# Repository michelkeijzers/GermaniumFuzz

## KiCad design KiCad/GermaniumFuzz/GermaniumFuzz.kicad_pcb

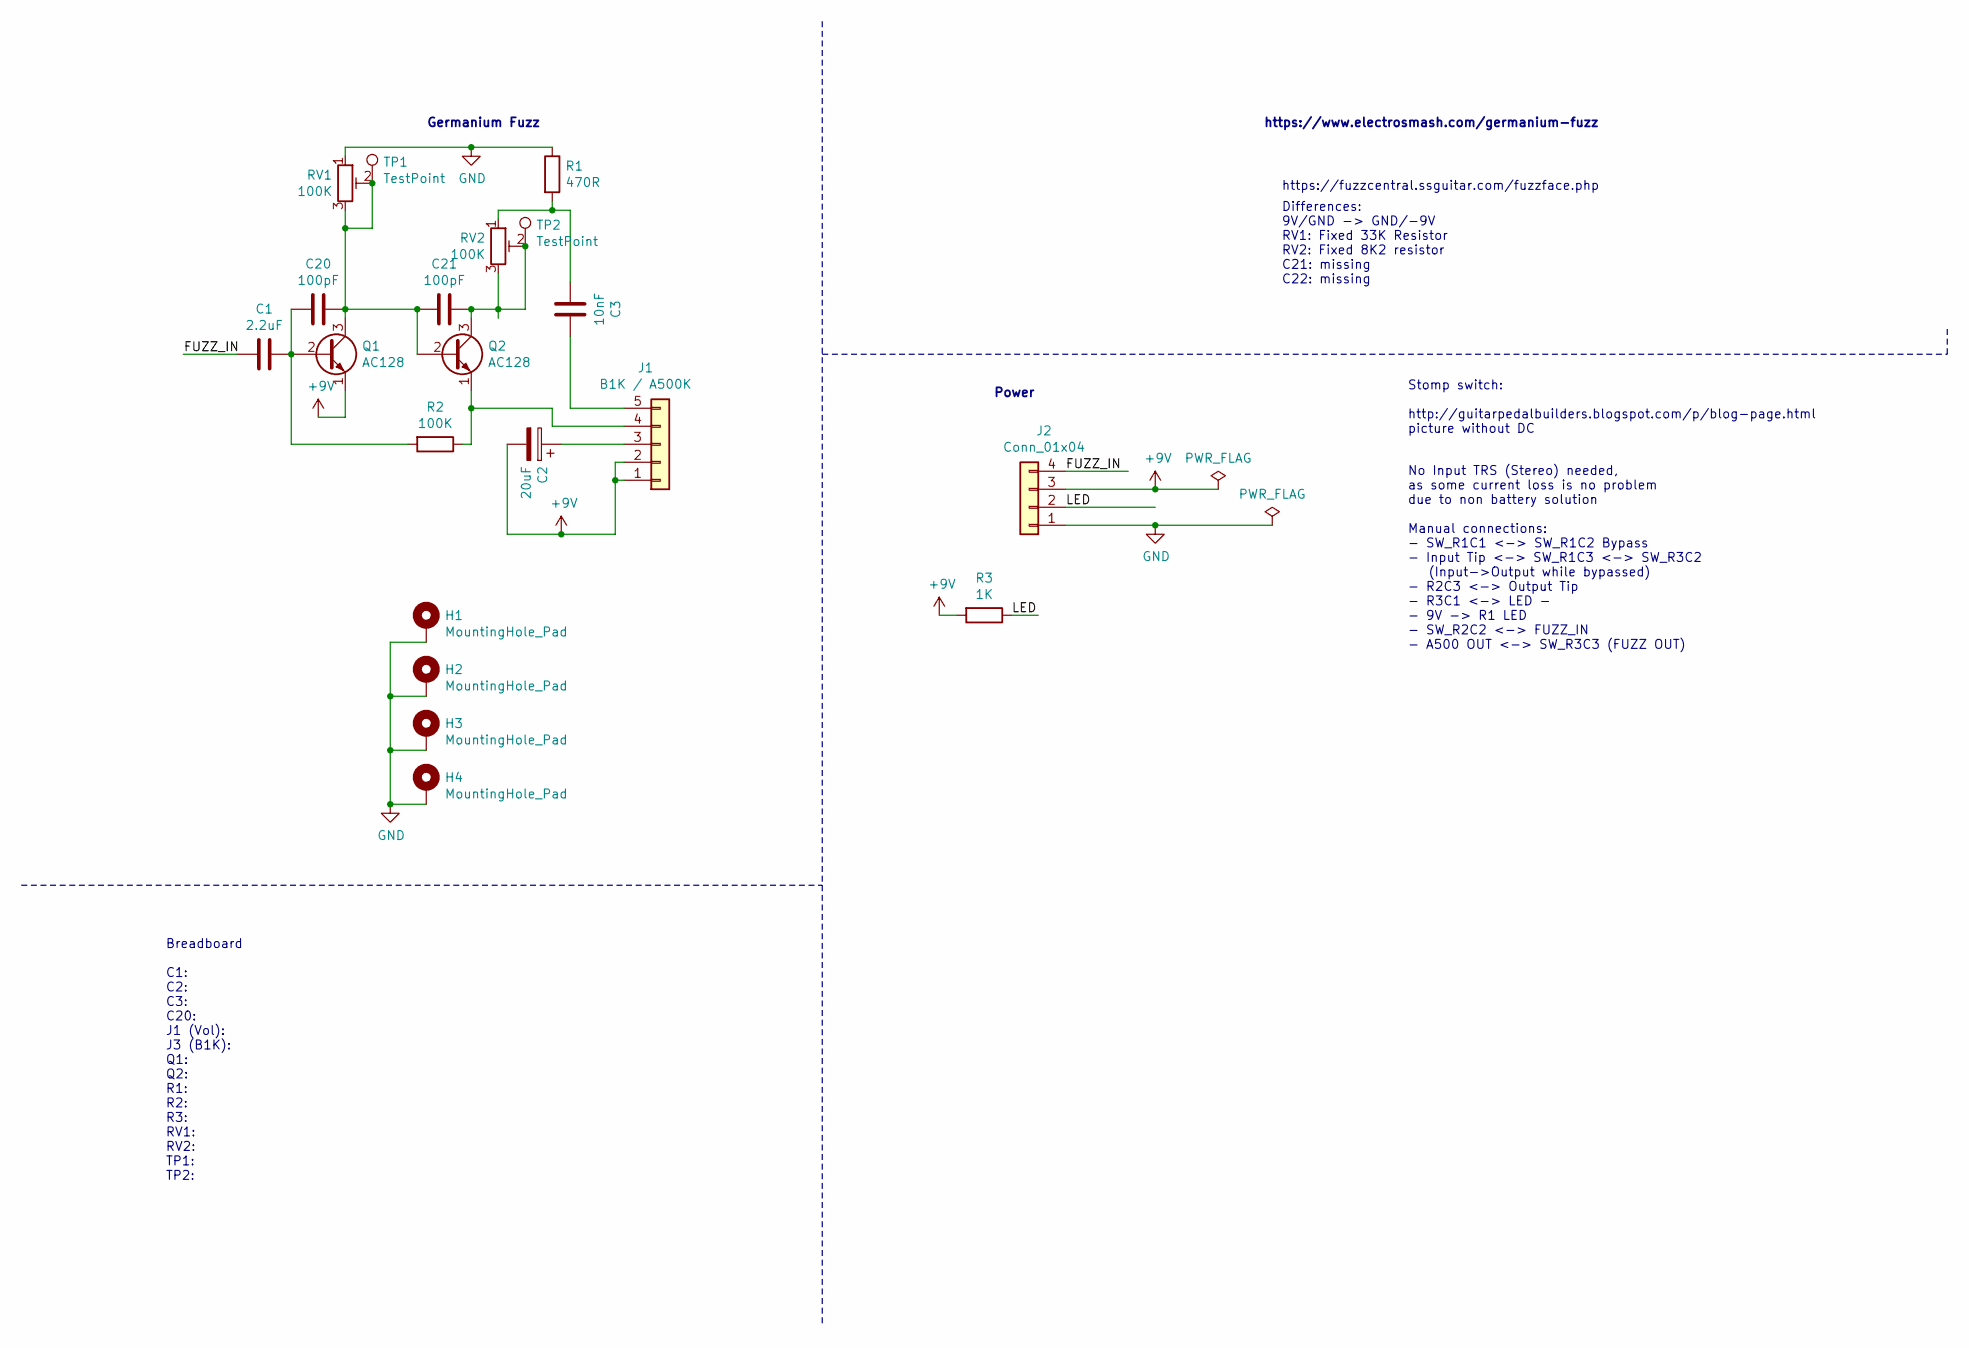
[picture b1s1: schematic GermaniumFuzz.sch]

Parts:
C1: 2.2uF; C_Disc_D3.0mm_W1.6mm_P2.50mm
C2: 20uF; C_Radial_D5.0mm_H11.0mm_P2.00mm
C3: 10nF; C_Disc_D3.0mm_W1.6mm_P2.50mm
C20, C21: 100pF; C_Disc_D3.0mm_W1.6mm_P2.50mm
H1, H2, H3, H4: MountingHole_Pad; MountingHole_3mm_Pad_Via
J1: B1K / A500K; JST_XH_B5B-XH-A_1x05_P2.50mm_Vertical
J2: Conn_01x04; JST_XH_B4B-XH-A_1x04_P2.50mm_Vertical
Q1, Q2: AC128; TO-92_Inline
R1: 470R; R_Axial_DIN0207_L6.3mm_D2.5mm_P7.62mm_Horizontal
R2: 100K; R_Axial_DIN0207_L6.3mm_D2.5mm_P7.62mm_Horizontal
R3: 1K; R_Axial_DIN0207_L6.3mm_D2.5mm_P7.62mm_Horizontal
RV1, RV2: 100K; Potentiometer_Vishay_T73XW_Horizontal
TP1, TP2: TestPoint; TestPoint_THTPad_D1.5mm_Drill0.7mm

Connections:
+9V: C2.2, J1.1, J1.2, J2.3, Q1.1 (E), R3.2
/FUZZ_IN: C1.2, J2.4
/LED: J2.2, R3.1
GND: H1.1, H2.1, H3.1, H4.1, J2.1, R1.1, RV1.1
unnamed: C1.1, C20.1, Q1.2 (B), R2.2
unnamed: C2.1, J1.3
unnamed: C3.1, J1.5
unnamed: C3.2, R1.2, RV2.1
unnamed: C20.2, C21.1, Q1.3 (C), Q2.2 (B), RV1.2, RV1.3, TP1.1
unnamed: C21.2, Q2.3 (C), RV2.2, RV2.3, TP2.1
unnamed: J1.4, Q2.1 (E), R2.1

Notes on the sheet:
https://www.electrosmash.com/germanium-fuzz
Germanium Fuzz
https://fuzzcentral.ssguitar.com/fuzzface.php
Differences: 9V/GND -> GND/-9V RV1: Fixed 33K Resistor RV2: Fixed 8K2 resistor C21: missing C22: missing
Stomp switch: http://guitarpedalbuilders.blogspot.com/p/blog-page.html picture without DC
No Input TRS (Stereo) needed, as some current loss is no problem due to non battery solution Manual connections: - SW_R1C1 <-> SW_R1C2 Bypass - Input Tip <-> SW_R1C3 <-> SW_R3C2 (Input->Output while bypassed) - R2C3 <-> Output Tip - R3C1 <-> LED - - 9V -> R1 LED - SW_R2C2 <-> FUZZ_IN - A500 OUT <->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
Power
Breadboard C1: C2: C3: C20: J1 (Vol): J3 (B1K): Q1: Q2: R1: R2: R3: RV1: RV2: TP1: TP2:

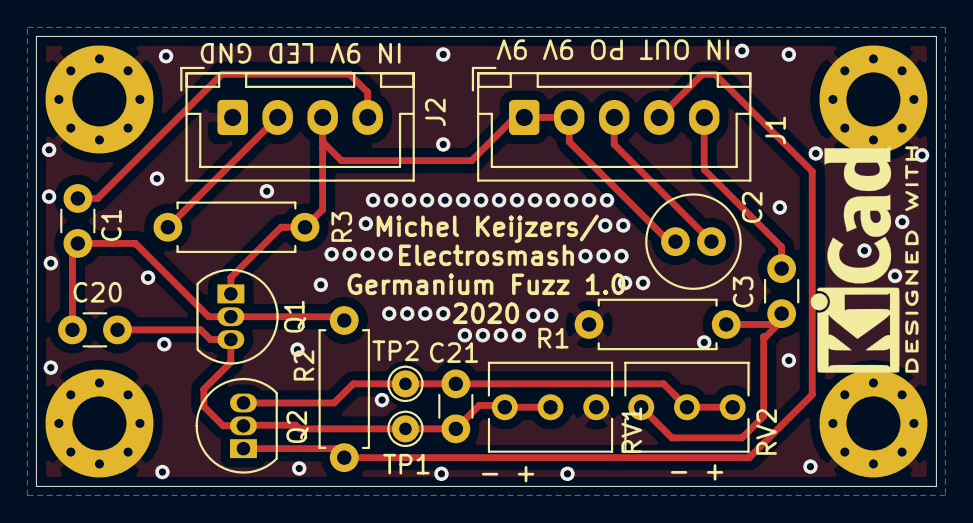
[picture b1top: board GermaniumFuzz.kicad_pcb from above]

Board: 2 copper layers, 50.0 x 25.0 mm, 20 parts (0 on the bottom side), 11 nets.

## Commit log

2020-07-02 Initial
    Initial
2020-07-02 Ignore
